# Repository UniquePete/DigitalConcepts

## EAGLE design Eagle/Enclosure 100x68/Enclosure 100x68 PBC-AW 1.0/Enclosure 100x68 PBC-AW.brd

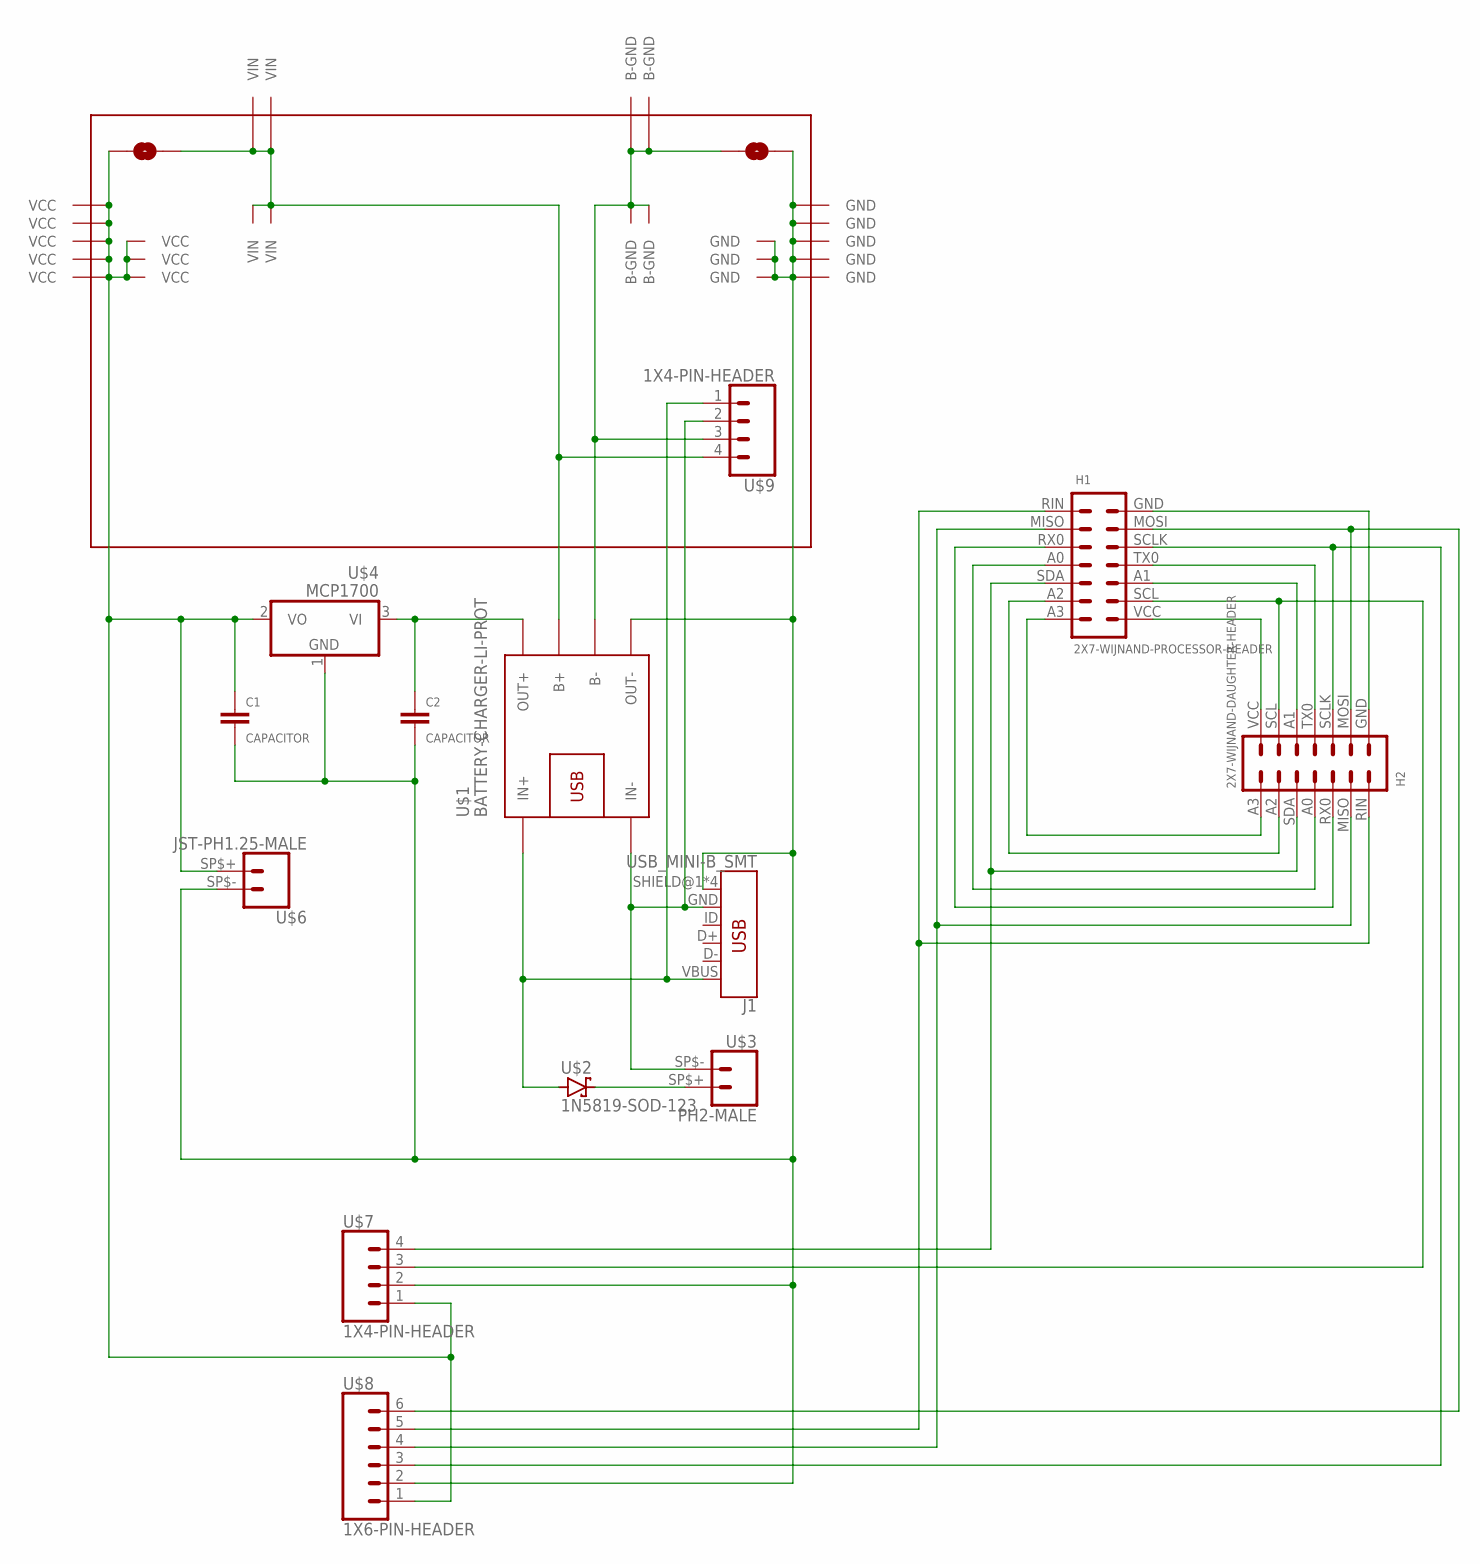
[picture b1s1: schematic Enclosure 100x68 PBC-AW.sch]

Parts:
C1, C2: CAPACITOR; C0805
H1: 2X7-WIJNAND-PROCESSOR-HEADER; 2X7-WIJNAND-PROCESSOR
H2: 2X7-WIJNAND-DAUGHTER-HEADER; 2X7-WIJNAND-DAUGHTER
J1: USB_MINI-B_SMT; USB-MINIB
U$1: BATTERY-CHARGER-LI-PROT
U$2: 1N5819-SOD-123; SOD-123
U$3: PH2-MALE; PH2
U$4: MCP1700; SOT23
U$5: PROTO-34X22-BAT-SJ-CHG-W
U$6: JST-PH1.25-MALE; JST-PH1.25
U$7, U$9: 1X4-PIN-HEADER; CONN_04-GENERIC
U$8: 1X6-PIN-HEADER; CONN_06-GENERIC

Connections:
GND: C1.2, C2.2, J1.SHIELD@1 (SHIELD), J1.SHIELD@2 (SHIELD), J1.SHIELD@3 (SHIELD), J1.SHIELD@4 (SHIELD), U$1.OUT-, U$4.1 (GND), U$5.GND, U$5.P33-13 (GND), U$5.P33-14 (GND), U$5.P33-15 (GND), U$5.P34-13 (GND), U$5.P34-14 (GND), U$5.P34-15 (GND), U$5.P34-16 (GND), U$5.P34-17 (GND), U$6.SP$- (2), U$7.2, U$8.2
unnamed: U$2.2 (C), U$3.SP$+ (1)
unnamed: J1.GND, U$1.IN-, U$3.SP$- (2), U$9.2
unnamed: U$1.B+, U$5.P02-17 (VIN), U$5.P03-16 (VIN), U$5.P05-19 (VIN), U$5.P06-19 (VIN), U$5.VIN, U$9.4
unnamed: U$1.B-, U$5.B-GND, U$5.P28-19 (B-GND), U$5.P30-19 (B-GND), U$5.P32-16 (B-GND), U$5.P33-17 (B-GND), U$9.3
unnamed: J1.VBUS, U$1.IN+, U$2.1 (A), U$9.1
unnamed: C2.1, U$1.OUT+, U$4.3 (VI)
unnamed: H1.VCC (1), H2.VCC (1)
unnamed: H1.SCL (2), H2.SCL (2), U$7.3
unnamed: H1.A1 (3), H2.A1 (3)
unnamed: H1.TX0 (4), H2.TX0 (4)
unnamed: H1.SCLK (5), H2.SCLK (5), U$8.3
unnamed: H1.MOSI (6), H2.MOSI (6), U$8.6
unnamed: H1.GND (7), H2.GND (7)
unnamed: H1.A3 (14), H2.A3 (14)
unnamed: H1.A2 (13), H2.A2 (13)
unnamed: H1.SDA (12), H2.SDA (12), U$7.4
unnamed: H1.A0 (11), H2.A0 (11)
unnamed: H1.RX0 (10), H2.RX0 (10)
unnamed: H1.MISO (9), H2.MISO (9), U$8.4
unnamed: H1.RIN (8), H2.RIN (8), U$8.5
VCC: C1.1, U$4.2 (VO), U$5.P01-13 (VCC), U$5.P01-14 (VCC), U$5.P01-15 (VCC), U$5.P01-16 (VCC), U$5.P01-17 (VCC), U$5.P02-13 (VCC), U$5.P02-14 (VCC), U$5.P02-15 (VCC), U$5.VCC, U$6.SP$+ (1), U$7.1, U$8.1

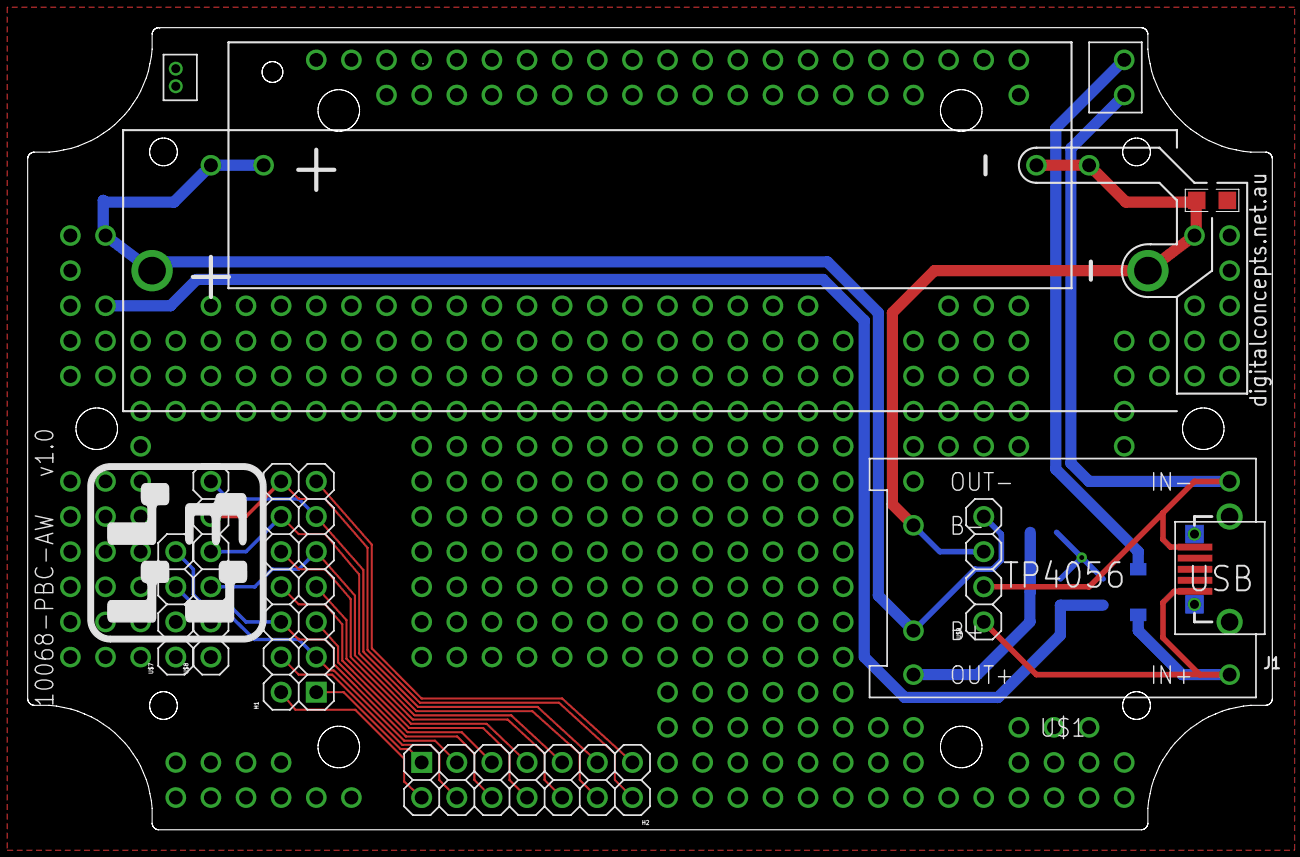
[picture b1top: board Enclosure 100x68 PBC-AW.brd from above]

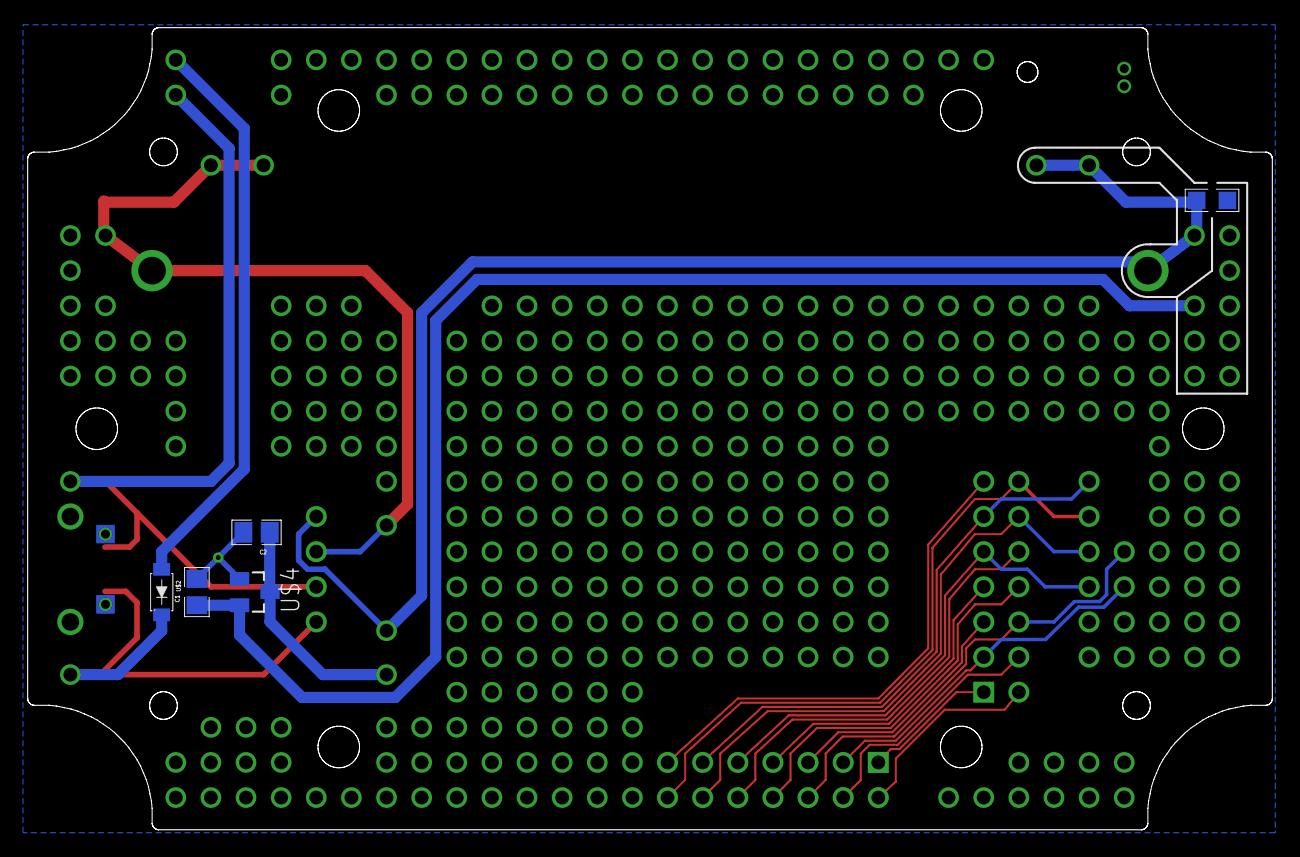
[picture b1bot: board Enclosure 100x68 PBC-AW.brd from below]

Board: 2 copper layers, 90.0 x 58.0 mm, 14 parts (4 on the bottom side), 22 nets.

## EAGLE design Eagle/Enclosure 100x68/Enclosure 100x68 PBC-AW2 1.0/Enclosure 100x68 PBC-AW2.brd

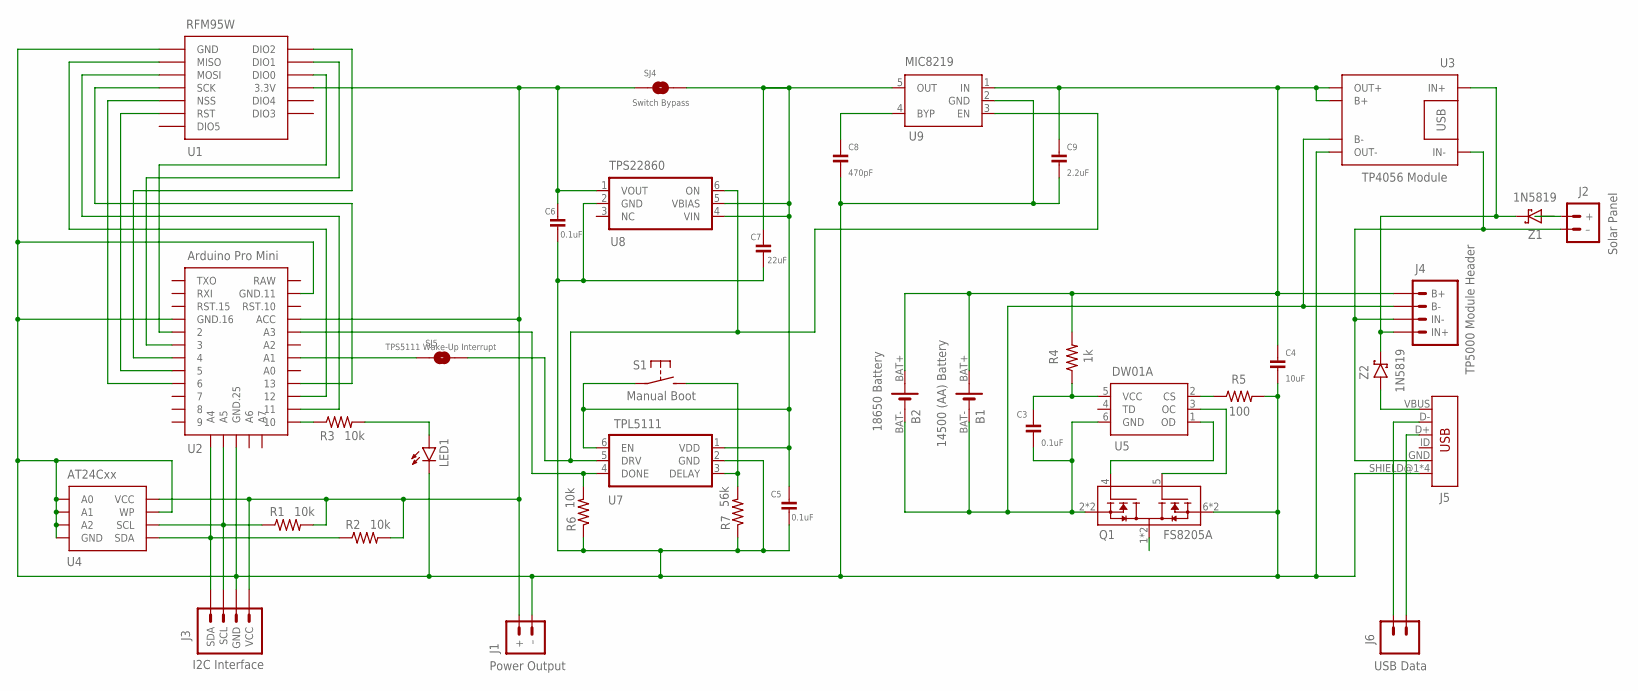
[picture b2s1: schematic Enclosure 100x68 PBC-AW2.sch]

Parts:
B1: 14500 (AA) Battery; BATTERY-14500
B2: 18650 Battery; BATTERY-18650
C3, C5, C6: 0.1uF; C0805
C4: 10uF; C0805
C7: 22uF; C0805
C8: 470pF; C0805
C9: 2.2uF; C0805
J1: Power Output; JST-PH1.25
J2: Solar Panel; JST-PH2.0
J3: I2C Interface; CONN_04-GENERIC
J4: TP5000 Module Header; CONN_04-GENERIC
J5: USB; USB-MINIB
J6: USB Data; CONN_02-GENERIC
LED1: LEDCHIP-LED0805; CHIP-LED0805
Q1: FS8205A; SOP65P640X120-8N
R1, R2, R3, R6: 10k; R0805
R4: 1k; R0805
R5: 100; R0805
R7: 56k; R0805
S1: Manual Boot; 2-PAD-SWITCH
SJ4: Switch Bypass; SJ
SJ5: TPS5111 Wake-Up Interrupt; SJ
U1: RFM95W; RFM95W-PI
U2: Arduino Pro Mini; PRO-MINI-29
U3: TP4056 Module; BATTERY-CHARGER-LI-PROT
U4: AT24Cxx; SOP-8
U5: DW01A; SOT23-6
U7: TPL5111; SOT-23-6
U8: TPS22860; SOT-23-6
U9: MIC8219; SOT-23-5
Z1, Z2: 1N5819; SOD-123

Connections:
GND: C4.2, C5.2, C6.2, C7.2, C8.2, C9.2, J1.- (–), J3.2 (GND), J5.SHIELD@1 (SHIELD), J5.SHIELD@2 (SHIELD), J5.SHIELD@3 (SHIELD), J5.SHIELD@4 (SHIELD), LED1.C, Q1.6 (S2), Q1.7 (S2), R5.2, R6.1, R7.1, U1.GND@3 (GND), U1.GND@6 (GND), U2.GND@11 (GND.25), U2.GND@16 (GND.16), U2.GND@25 (GND.11), U3.OUT-, U4.P$1 (A0), U4.P$2 (A1), U4.P$3 (A2), U4.P$4 (GND), U4.P$7 (WP), U7.2 (GND), U8.2 (GND), U9.2 (GND)
unnamed: J2.+, Z1.A
unnamed: J2.- (–), J4.2 (IN-), J5.GND, U3.IN-
unnamed: R5.1, U5.2 (CS)
unnamed: Q1.1 (D12), Q1.8 (D12)
unnamed: J4.1 (IN+), U3.IN+, Z1.C, Z2.C
unnamed: B1.BAT+, B2.BAT+, C4.1, C9.1, J4.4 (B+), R4.2, U3.B+, U3.OUT+, U9.1 (IN)
unnamed: C8.1, U9.4 (BYP)
unnamed: J3.3 (SCL), R1.1, U2.A5, U4.P$6 (SCL)
unnamed: U1.MISO, U2.12
unnamed: U1.MOSI, U2.11
unnamed: U1.SCK, U2.13
unnamed: R3.1, U2.10
unnamed: U1.RST, U2.5
unnamed: U1.DIO2, U2.4
unnamed: U1.DIO1, U2.3
unnamed: U1.DIO0, U2.2
unnamed: LED1.A, R3.2
unnamed: Q1.5 (G2), U5.3 (OC)
unnamed: J5.VBUS, Z2.A
unnamed: Q1.4 (G1), U5.1 (OD)
unnamed: J5.D+, J6.2
unnamed: C3.1, R4.1, U5.5 (VCC)
unnamed: B1.BAT-, B2.BAT-, C3.2, J4.3 (B-), Q1.2 (S1), Q1.3 (S1), U3.B-, U5.6 (GND)
unnamed: J5.D-, J6.1
unnamed: R7.2, S1.P$2 (S), U7.3 (DELAY)
unnamed: C5.1, C7.1, S1.P$1, SJ4.2, U7.1 (VDD), U7.6 (EN), U8.4 (VIN), U8.5 (VBIAS), U9.5 (OUT)
unnamed: J3.4 (SDA), R2.1, U2.A4, U4.P$5 (SDA)
unnamed: SJ5.2, U7.5 (DRV), U8.6 (ON), U9.3 (EN)
unnamed: R6.2, U2.A3, U7.4 (DONE)
unnamed: SJ5.1, U2.A1
NSS: U1.NSS, U2.6
RAW: U2.RAW
VCC: C6.1, J1.+, J3.1 (VCC), R1.2, R2.2, SJ4.1, U1.3V3 (3.3V), U2.ACC, U4.P$8 (VCC), U8.1 (VOUT)

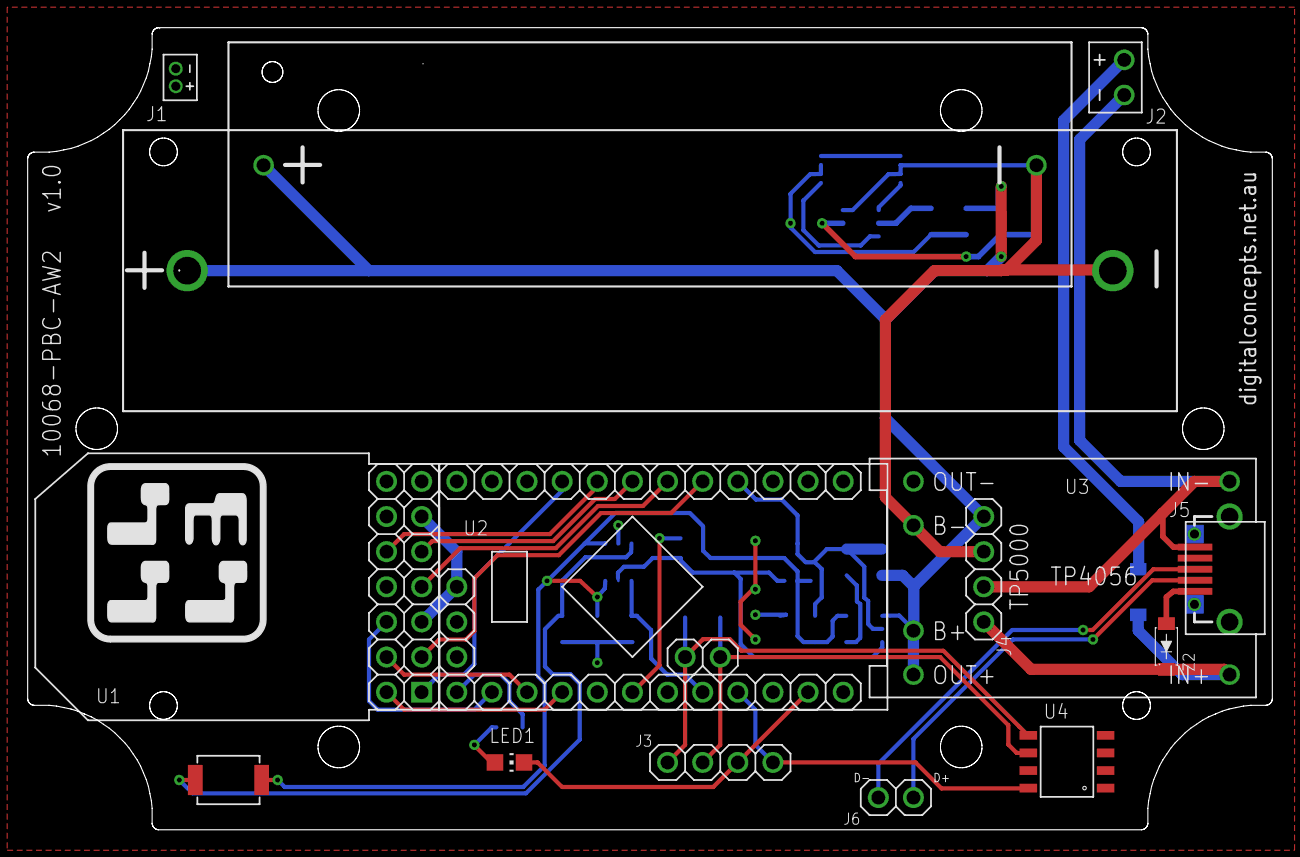
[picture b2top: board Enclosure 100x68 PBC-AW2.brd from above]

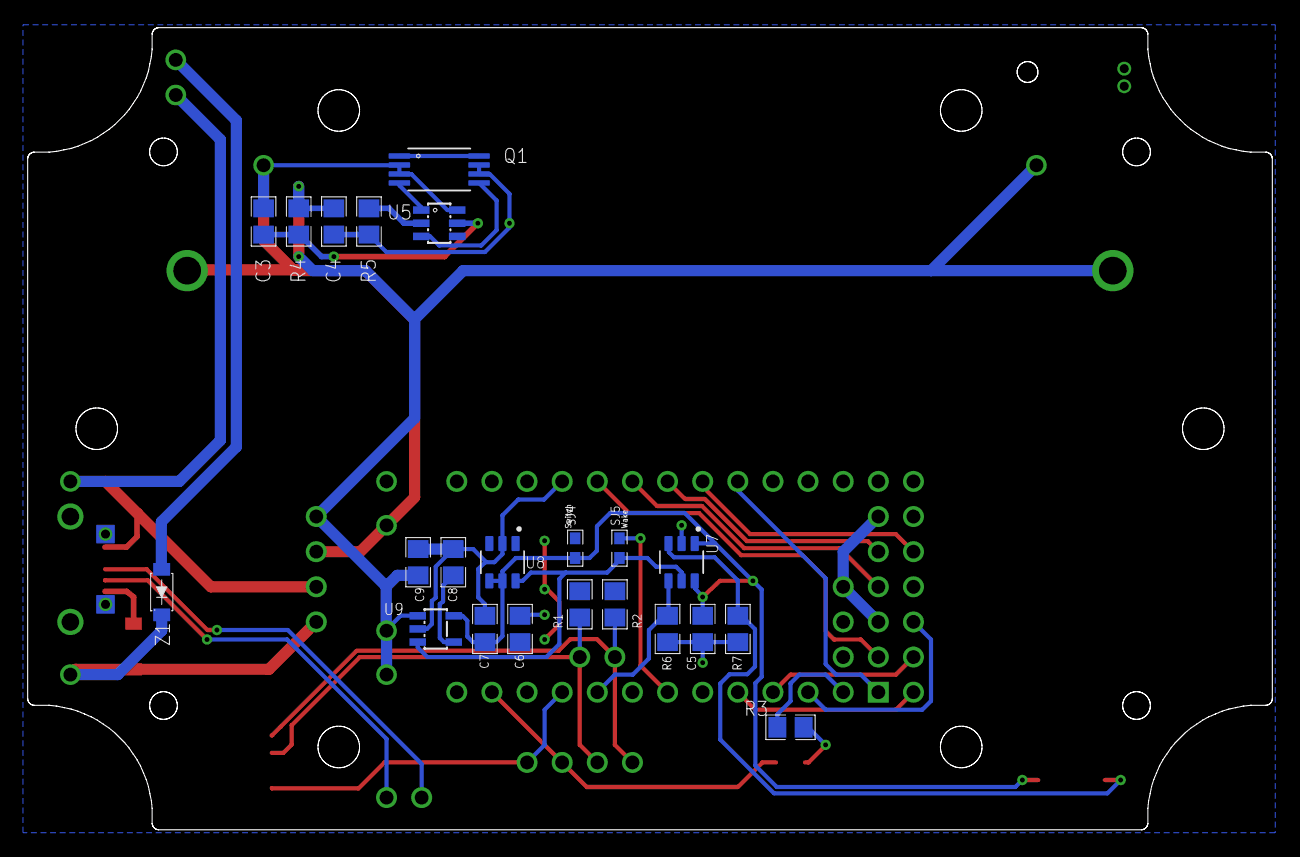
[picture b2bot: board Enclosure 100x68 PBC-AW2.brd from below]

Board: 2 copper layers, 90.0 x 58.0 mm, 37 parts (22 on the bottom side), 33 nets.

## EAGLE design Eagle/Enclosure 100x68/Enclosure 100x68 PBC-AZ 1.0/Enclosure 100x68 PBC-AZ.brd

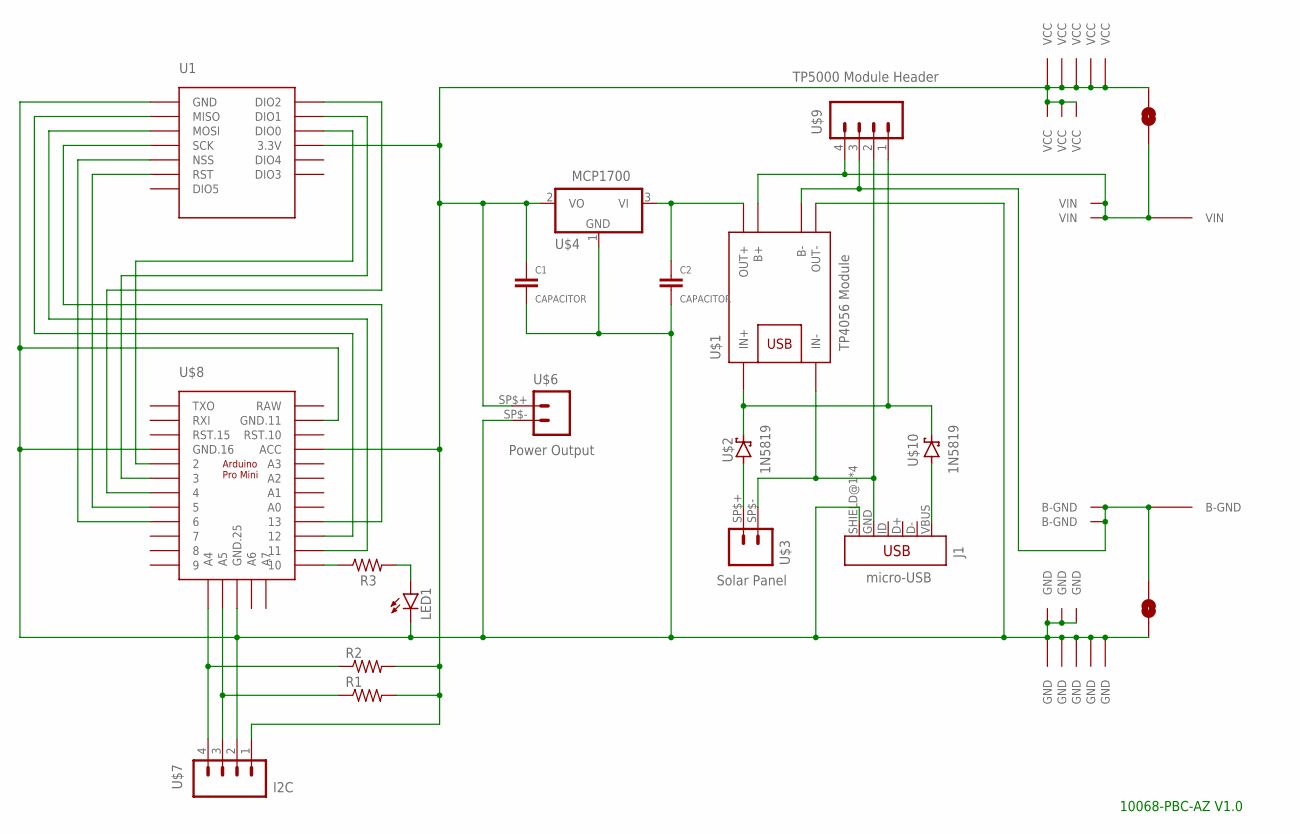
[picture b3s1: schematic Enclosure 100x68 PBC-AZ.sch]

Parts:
C1, C2: CAPACITOR; C0805
J1: micro-USB; USB-MINIB
LED1: LEDCHIP-LED0805; CHIP-LED0805
R1, R2, R3: RESISTORR0805; R0805
U1: RFM95W-PI
U$1: TP4056 Module; BATTERY-CHARGER-LI-PROT
U$2, U$10: 1N5819; SOD-123
U$3: Solar Panel; JST-PH2.0
U$4: MCP1700; SOT23
U$5: PROTO-34X22-BAT-SJ-CHG-Z
U$6: Power Output; JST-PH1.25
U$7: I2C; CONN_04-GENERIC
U$8: ARDUINO-PRO-MINI; PRO-MINI-29
U$9: TP5000 Module Header; CONN_04-GENERIC

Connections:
GND: C1.2, C2.2, J1.SHIELD@1 (SHIELD), J1.SHIELD@2 (SHIELD), J1.SHIELD@3 (SHIELD), J1.SHIELD@4 (SHIELD), LED1.C, U1.GND@3 (GND), U1.GND@6 (GND), U$1.OUT-, U$4.1 (GND), U$5.GND, U$5.P33-13 (GND), U$5.P33-14 (GND), U$5.P33-15 (GND), U$5.P34-13 (GND), U$5.P34-14 (GND), U$5.P34-15 (GND), U$5.P34-16 (GND), U$5.P34-17 (GND), U$6.SP$- (2), U$7.2, U$8.GND@11 (GND.25), U$8.GND@16 (GND.16), U$8.GND@25 (GND.11)
unnamed: U$2.A, U$3.SP$+ (1)
unnamed: J1.GND, U$1.IN-, U$3.SP$- (2), U$9.2
unnamed: U$1.B-, U$5.B-GND, U$5.P28-19 (B-GND), U$5.P32-16 (B-GND), U$5.P33-17 (B-GND), U$9.3
unnamed: U$1.B+, U$5.P02-17 (VIN), U$5.P03-16 (VIN), U$5.P06-19 (VIN), U$5.VIN, U$9.4
unnamed: U$1.IN+, U$2.C, U$9.1, U$10.C
unnamed: C2.1, U$1.OUT+, U$4.3 (VI)
unnamed: R2.1, U$7.4, U$8.A4
unnamed: R1.1, U$7.3, U$8.A5
unnamed: U1.MISO, U$8.12
unnamed: U1.MOSI, U$8.11
unnamed: U1.SCK, U$8.13
unnamed: R3.1, U$8.10
unnamed: U1.RST, U$8.5
unnamed: U1.DIO2, U$8.4
unnamed: U1.DIO1, U$8.3
unnamed: U1.DIO0, U$8.2
unnamed: LED1.A, R3.2
unnamed: J1.VBUS, U$10.A
NSS: U1.NSS, U$8.6
RAW: U$8.RAW
VCC: C1.1, R1.2, R2.2, U1.3V3 (3.3V), U$4.2 (VO), U$5.P01-13 (VCC), U$5.P01-14 (VCC), U$5.P01-15 (VCC), U$5.P01-16 (VCC), U$5.P01-17 (VCC), U$5.P02-13 (VCC), U$5.P02-14 (VCC), U$5.P02-15 (VCC), U$5.VCC, U$6.SP$+ (1), U$7.1, U$8.ACC

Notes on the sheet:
10068-PBC-AZ V1.0

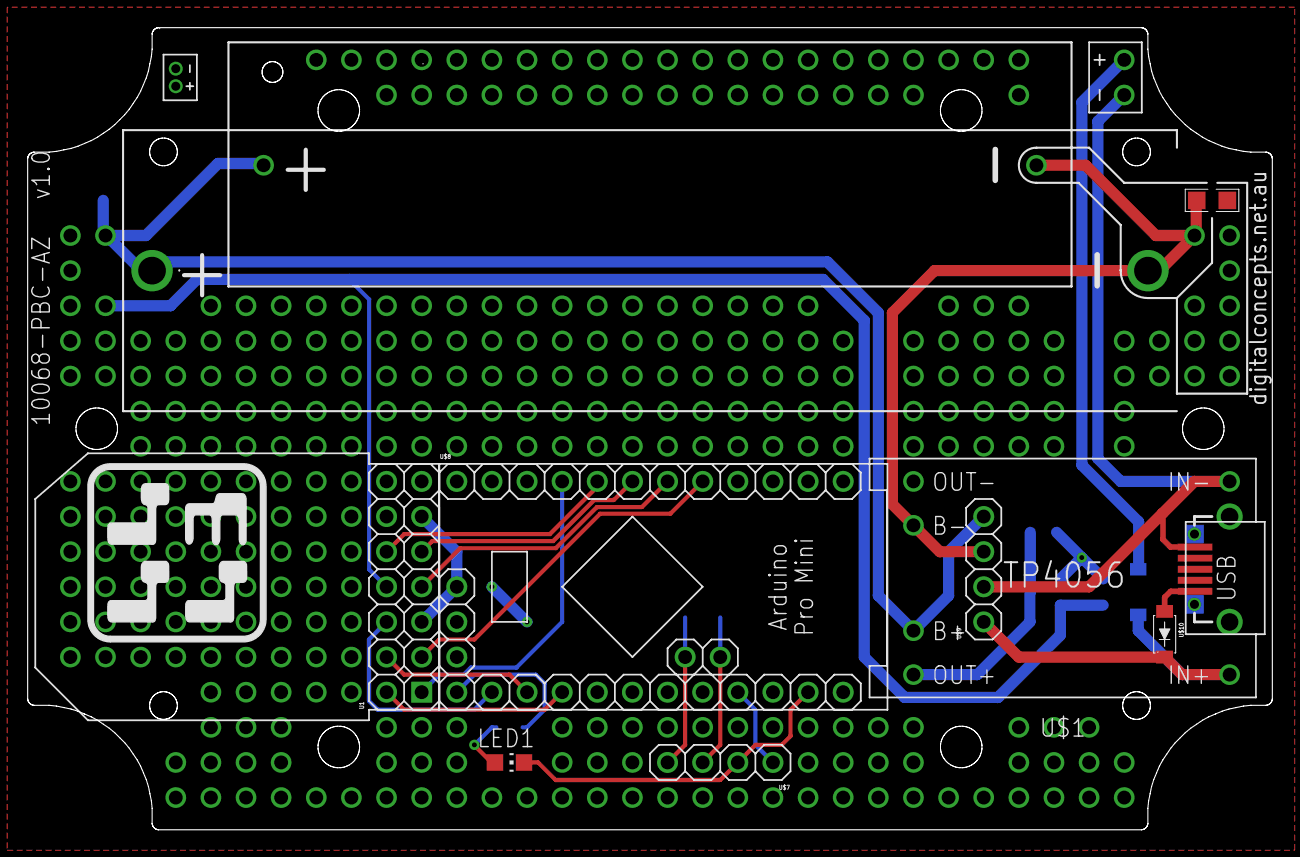
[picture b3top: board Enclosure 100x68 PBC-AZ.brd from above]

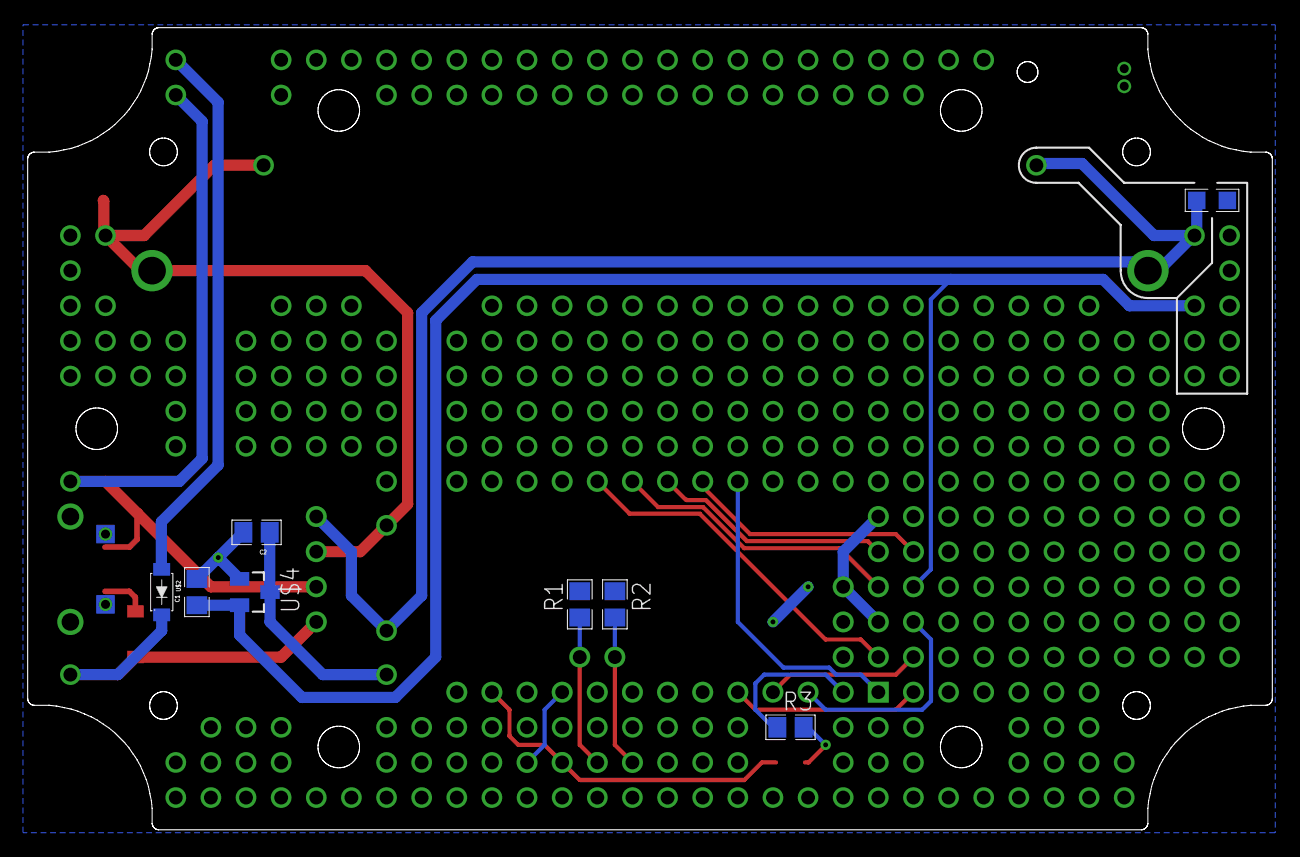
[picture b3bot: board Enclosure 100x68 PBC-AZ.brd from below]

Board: 2 copper layers, 90.0 x 58.0 mm, 18 parts (7 on the bottom side), 21 nets.

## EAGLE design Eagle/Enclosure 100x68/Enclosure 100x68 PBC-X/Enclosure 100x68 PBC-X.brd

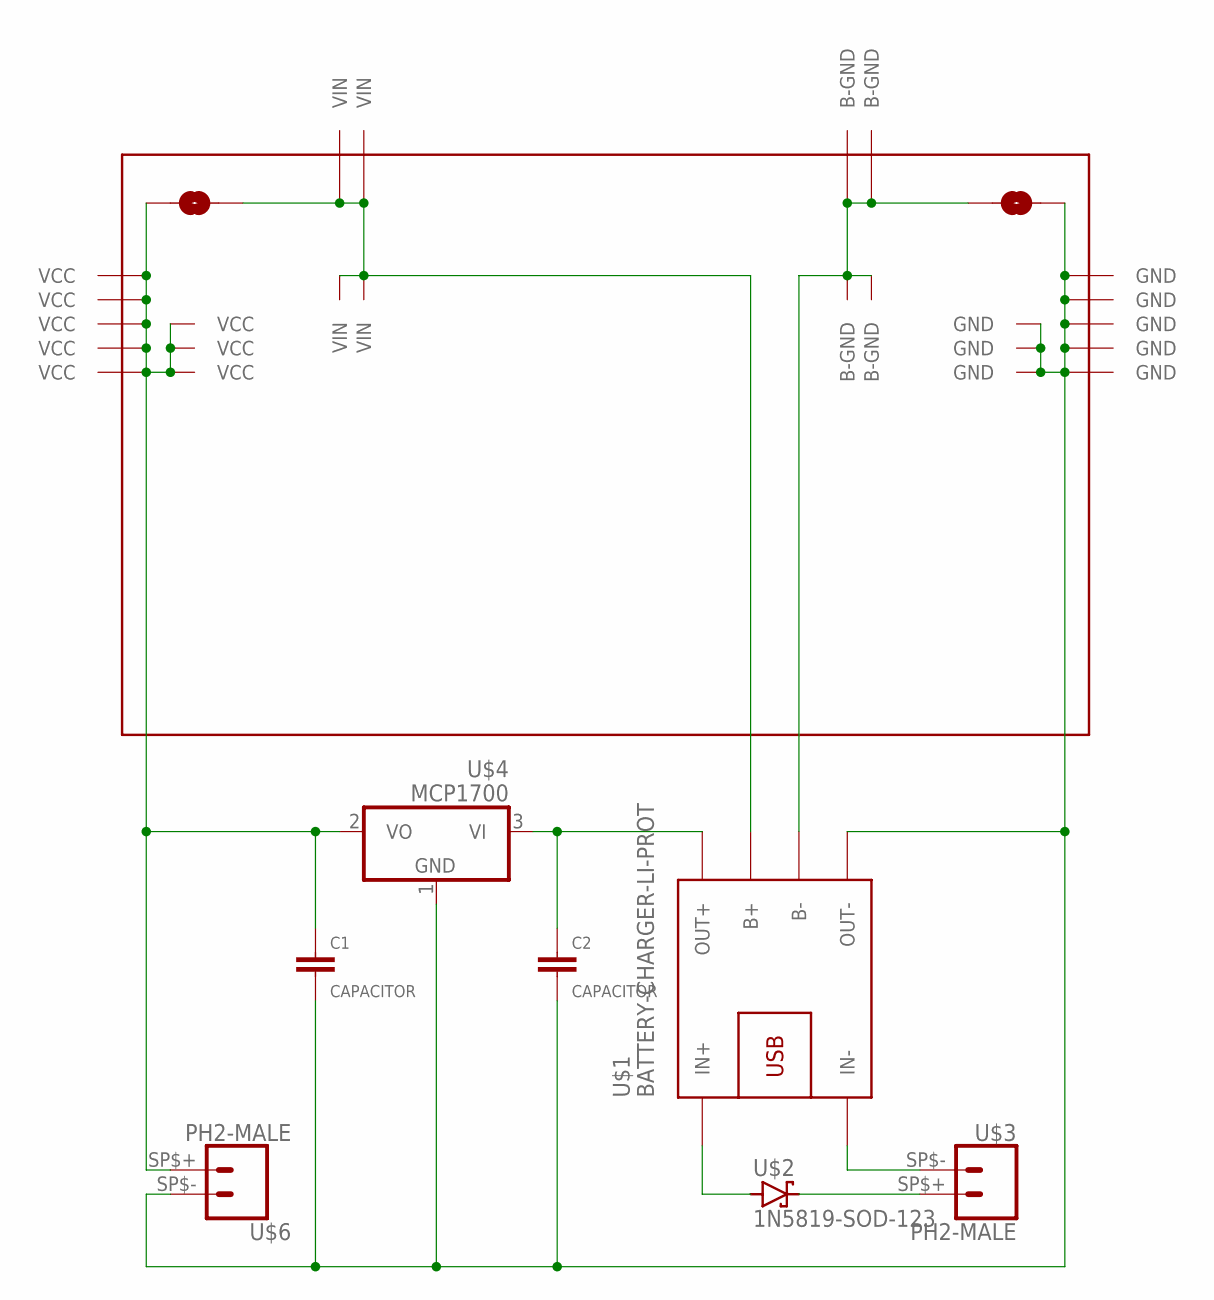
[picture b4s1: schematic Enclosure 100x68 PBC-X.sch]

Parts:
C1, C2: CAPACITOR; C0805
U$1: BATTERY-CHARGER-LI-PROT
U$2: 1N5819-SOD-123; SOD-123
U$3, U$6: PH2-MALE; PH2
U$4: MCP1700; SOT23
U$5: PROTO-34X22-BAT-SJ-CHG

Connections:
GND: C1.2, C2.2, U$1.OUT-, U$4.1 (GND), U$5.GND, U$5.P33-13 (GND), U$5.P33-14 (GND), U$5.P33-15 (GND), U$5.P34-13 (GND), U$5.P34-14 (GND), U$5.P34-15 (GND), U$5.P34-16 (GND), U$5.P34-17 (GND), U$6.SP$- (2)
unnamed: U$2.2 (C), U$3.SP$+ (1)
unnamed: U$1.IN-, U$3.SP$- (2)
unnamed: U$1.B+, U$5.P02-17 (VIN), U$5.P03-16 (VIN), U$5.P05-19 (VIN), U$5.P06-19 (VIN), U$5.VIN
unnamed: U$1.B-, U$5.B-GND, U$5.P28-19 (B-GND), U$5.P30-19 (B-GND), U$5.P32-16 (B-GND), U$5.P33-17 (B-GND)
unnamed: U$1.IN+, U$2.1 (A)
unnamed: C2.1, U$1.OUT+, U$4.3 (VI)
VCC: C1.1, U$4.2 (VO), U$5.P01-13 (VCC), U$5.P01-14 (VCC), U$5.P01-15 (VCC), U$5.P01-16 (VCC), U$5.P01-17 (VCC), U$5.P02-13 (VCC), U$5.P02-14 (VCC), U$5.P02-15 (VCC), U$5.VCC, U$6.SP$+ (1)

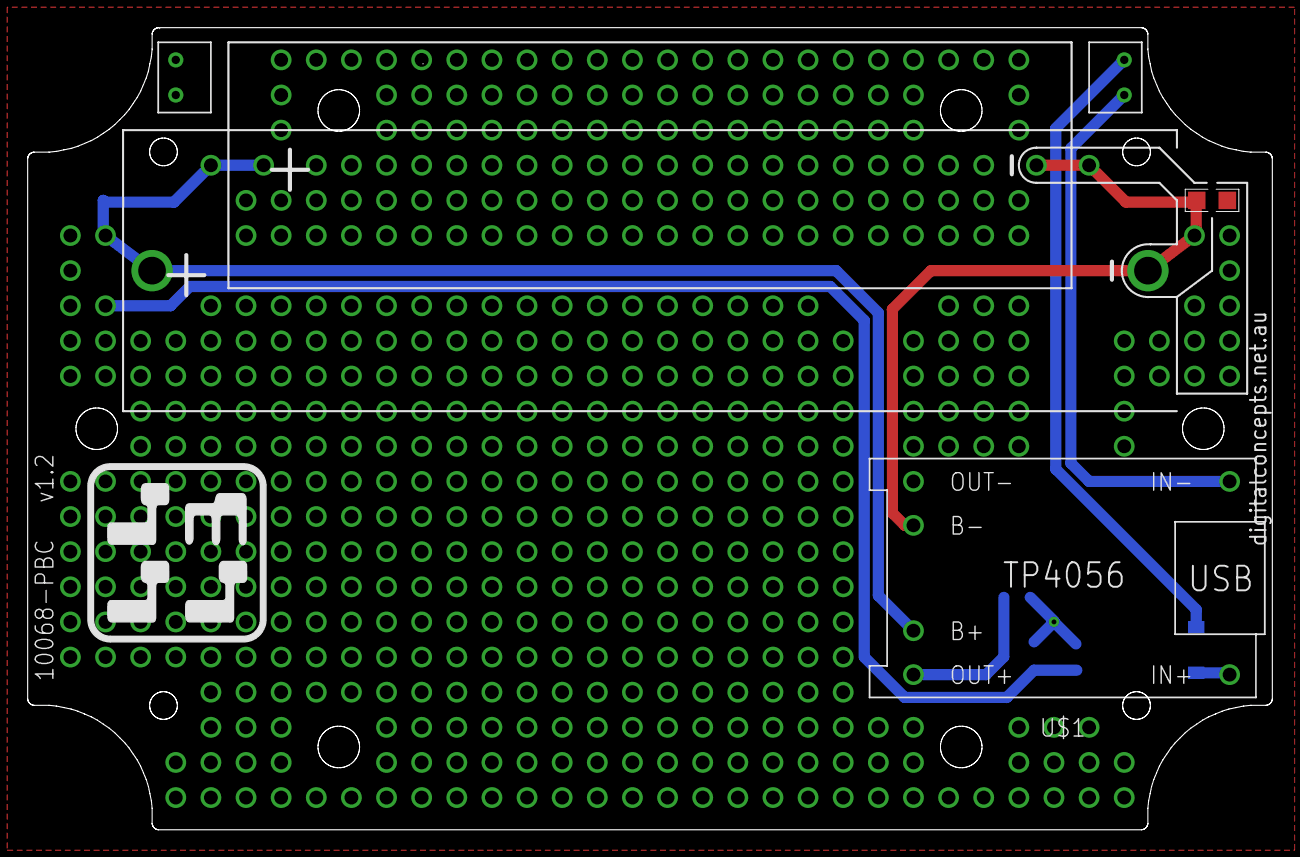
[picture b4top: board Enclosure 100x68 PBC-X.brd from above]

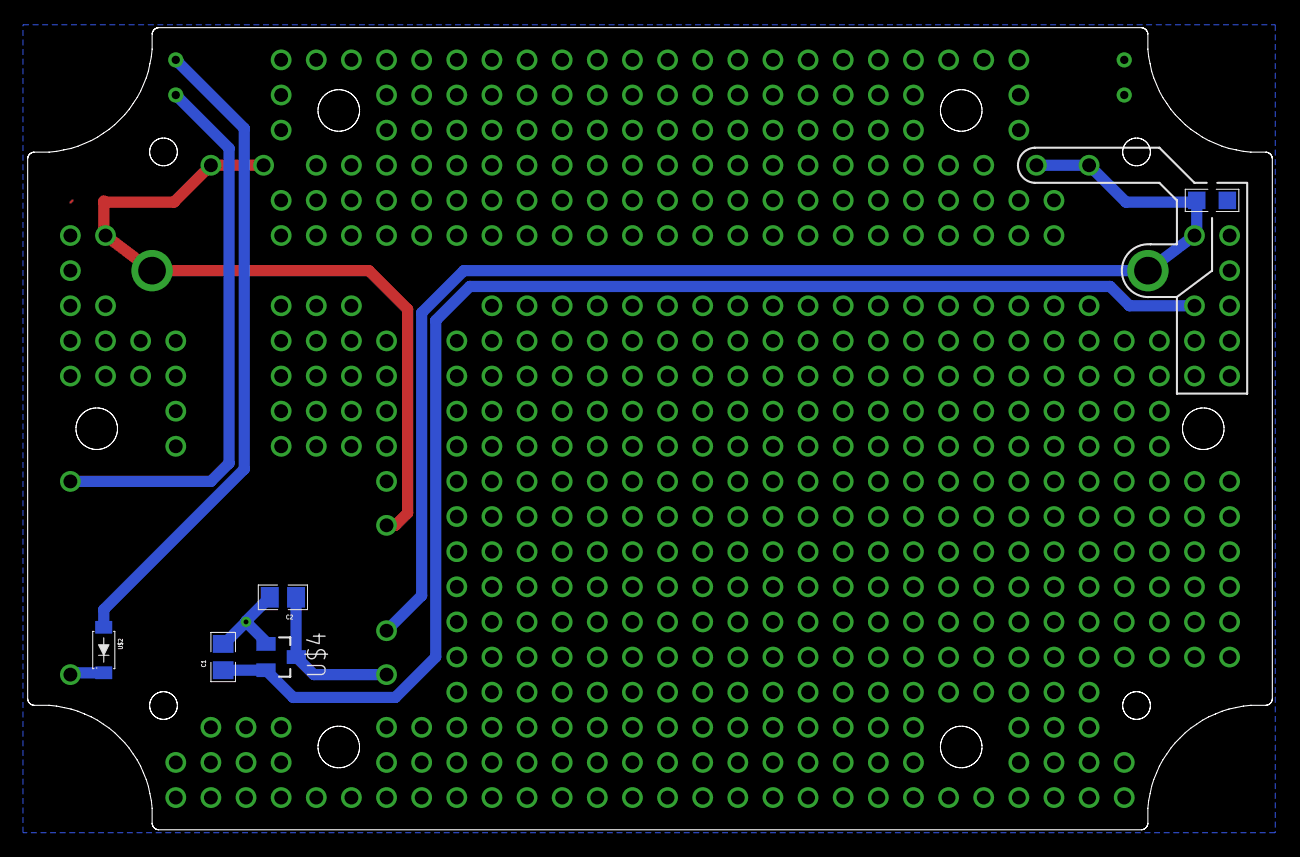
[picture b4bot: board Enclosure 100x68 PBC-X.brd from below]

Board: 2 copper layers, 90.0 x 58.0 mm, 8 parts (4 on the bottom side), 8 nets.
